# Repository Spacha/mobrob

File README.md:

# mobrob

A mobile robot 

## Features

* Obstacle detection and avoidance
* Room mapping (explore mode?)
* Manual control (throttle + steer)
  * For example, through browser-based GUI
* Automatic navigation (A to B) (after exploring space?)
  * Complete more complex tasks like _fetch an item_?
* Charging capability preferable (e.g. MCP73831)
  * https://www.youtube.com/watch?v=GRd9uTwg7r4&ab_channel=MicroTypeEngineering
  * https://www.youtube.com/watch?v=TyaW8ZKumno&ab_channel=PlumPot

# Initial design

Datasheets for components are found in `Datasheets` folder.

* **Processor & connectivity**: ESP8266 | [datasheet](datasheets/ESP8266EX_datasheet-v4.4.pdf)
  * These values are for ESP8266EX
  * WiFi: 802.11 b/g/n Wifi, 2.4-2.5 GHz
  * Peripherals: UART / SDIO / SPI / I2C / I2S / IR Remote Control / GPIO / PWM
  * Operating voltage 3.3V (3.0-3.6V)
  * Average operating current: 80 mA
  * Around 50 kB RAM (for user, when connected to a station)
  * **Requires external SPI flash!** Up to 16 MB flash can be supported
    * Suggested: 512 kB (without OTA), 1 MB (with OTA)
  * Single core, 80 MHz
* **Dual H-bridge motor driver**: L293D | [datasheet](datasheets/L293x_datasheet.pdf)
* Power management:
  * **Battery**: 11.1V Li-Po (6-12V), (3 x 3.7V cells)
    * Price: $20-40
  * **Buck converter (12V->5V)**: LM2596 or other...
    * https://www.youtube.com/watch?v=C7-8nUU6e3E&t=2367s
  * **LDO (5V->3.3V)**: LM7805
    * https://electronics.stackexchange.com/questions/420999/use-5v-linear-regulator-and-ldo-3-3v

* **Motors & chassis**: Dual motor tank chassis (3-7V)
  * https://www.aliexpress.com/item/4000115994387.html?spm=a2g0o.order_list.0.0.21ef1802jPbMxm
  * Has slot for 4xAA batteries, could be modified to fit the rechargable 3-cell Li-Po battery.
  * Size: 9.7cm x 18.5cm x 5cm (width x length x height )
  * Motors: 130 size generic, can be replaced if necessary
  * Price: $18.50

* Sensors (both for proximity and distance, and other):
  * IMU?
  * UT/IR?
  * Others?

# Discussion

I am not sure if either ESP32 or ESP8266 come in QFP format (only in QFN, no-leads). I guess JLCPCB and others also assemble these devices so maybe this is not an issue.

## ESP32
ESP32 would be considerably better than ESP8266. It has a lot more functionality and also has 8MB of onboard flash (ESP32-S3FN8, see ESP32-S3 datasheet, p.11).

* https://www.youtube.com/watch?v=WWIy6a0T7WM&ab_channel=PlumPot
* Decoupling caps (as close of the pins as possible)
* External crystal? (see Phil's lab)
* Note the antenna/RF part!
  * No traces (or any copper) beneath the antenna part!
* Careful with differential pairs

* https://en.wikipedia.org/wiki/ESP32#ESP32-S3:
  * ESP32-WROOM-32D: PCB trace antenna, 4 MiB flash (probably preferable)
  * ESP32-WROOM-32U: U.FL socket antenna, 4 MiB flash

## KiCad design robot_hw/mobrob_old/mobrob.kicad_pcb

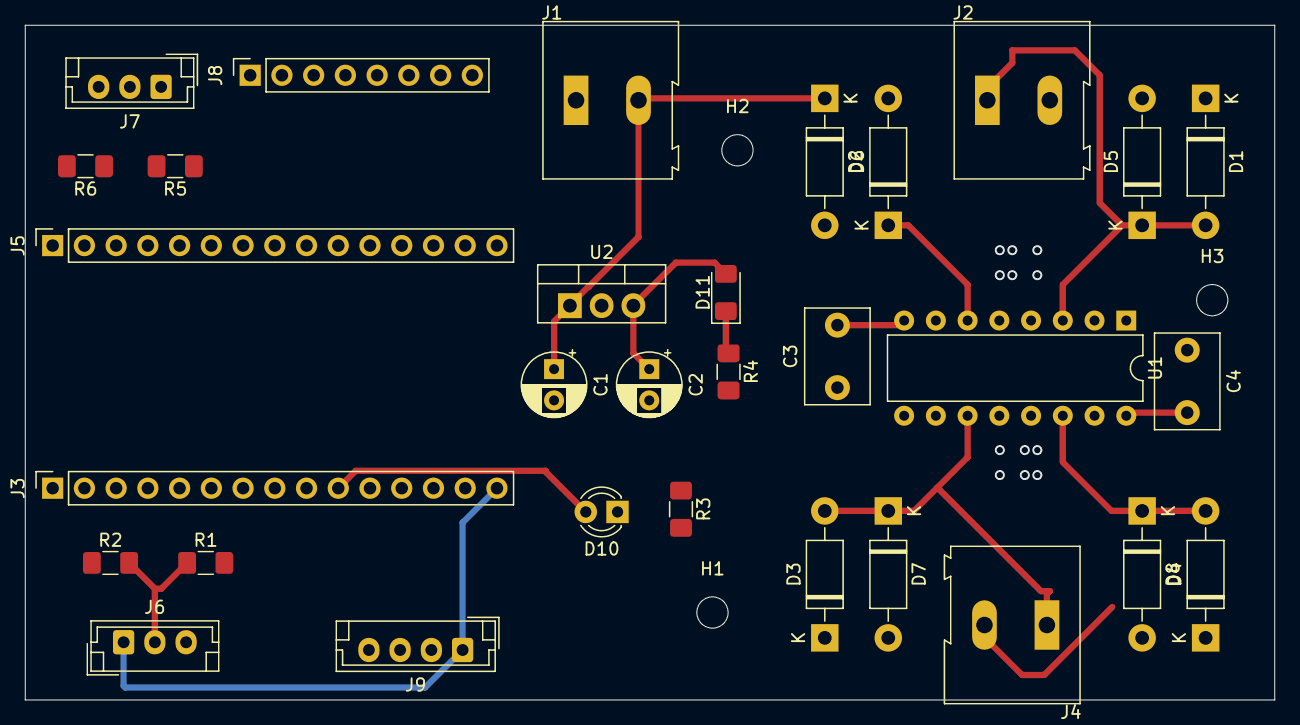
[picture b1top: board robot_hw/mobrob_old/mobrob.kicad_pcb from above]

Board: 2 copper layers, 100.0 x 54.0 mm, 34 parts (0 on the bottom side), 24 nets.

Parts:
C1: 0.22uF; CP_Radial_D5.0mm_P2.50mm
C2: 0.1uF; CP_Radial_D5.0mm_P2.50mm
C3, C4: 0.1uF; C_Disc_D7.5mm_W5.0mm_P5.00mm
D1, D2, D3, D4, D5, D6, D7, D8: 1N4007; D_DO-41_SOD81_P10.16mm_Horizontal
D10: LED_STATUS; LED_D3.0mm
D11: LED_POWER; LED_1206_3216Metric_Pad1.42x1.75mm_HandSolder
H1, H2, H3: MountingHole; MountingHole_2.5mm
J1: POWER; TerminalBlock_Altech_AK300-2_P5.00mm
J2: RMOTOR_OUT; TerminalBlock_Altech_AK300-2_P5.00mm
J3: MCU_ROW1; PinSocket_1x15_P2.54mm_Vertical
J4: LMOTOR_OUT; TerminalBlock_Altech_AK300-2_P5.00mm
J5: MCU_ROW2; PinSocket_1x15_P2.54mm_Vertical
J6: LHALL; JST_EH_B3B-EH-A_1x03_P2.50mm_Vertical
J7: RHALL; JST_EH_B3B-EH-A_1x03_P2.50mm_Vertical
J8: IMU; PinSocket_1x08_P2.54mm_Vertical
J9: UT; JST_EH_B4B-EH-A_1x04_P2.50mm_Vertical
R1, R6: 33k; R_1206_3216Metric_Pad1.42x1.75mm_HandSolder
R2, R5: 15k; R_1206_3216Metric_Pad1.42x1.75mm_HandSolder
R3, R4: 150; R_1206_3216Metric_Pad1.42x1.75mm_HandSolder
U1: L293D; DIP-16_W7.62mm
U2: L7805; TO-220-3_Vertical

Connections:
1,2EN: J3.7, U1.1
1A: J3.6, U1.2
2A: J3.12, U1.7
3,4EN: J3.9, U1.9
3A: J3.8, U1.10
4A: J3.13, U1.15
+5V: C2.1, C4.2, D11.2, J3.15, J6.1, J7.1, J8.1, J9.1, U1.16, U2.3
+12V: C1.1, C3.2, D1.1, D2.1, D3.1, D4.1, J1.2, U1.8, U2.1
GND: C1.2, C2.2, C3.1, C4.1, D5.2, D6.2, D7.2, D8.2, J1.1, J3.14, J5.14, J6.3, J7.3, J8.2, J9.4, R1.2, R3.1, R4.2, R6.2, U1.4, U1.5, U1.12, U1.13, U2.2
IMU_SCL: J5.2, J8.3
IMU_SDA: J5.5, J8.4
LED_STATUS: D10.2, J3.10
LHALL_IN: J3.3, R2.1
unnamed: D1.2, D5.1, J2.1, U1.3
unnamed: D2.2, D6.1, J2.2, U1.6
unnamed: D3.2, D7.1, J4.1, U1.11
unnamed: D4.2, D8.1, J4.2, U1.14
unnamed: D10.1, R3.2
unnamed: D11.1, R4.1
unnamed: J6.2, R1.1, R2.2
unnamed: J7.2, R5.2, R6.1
RHALL_IN: J3.2, R5.1
UT_ECHO: J5.1, J9.3
UT_TRIG: J5.11, J9.2

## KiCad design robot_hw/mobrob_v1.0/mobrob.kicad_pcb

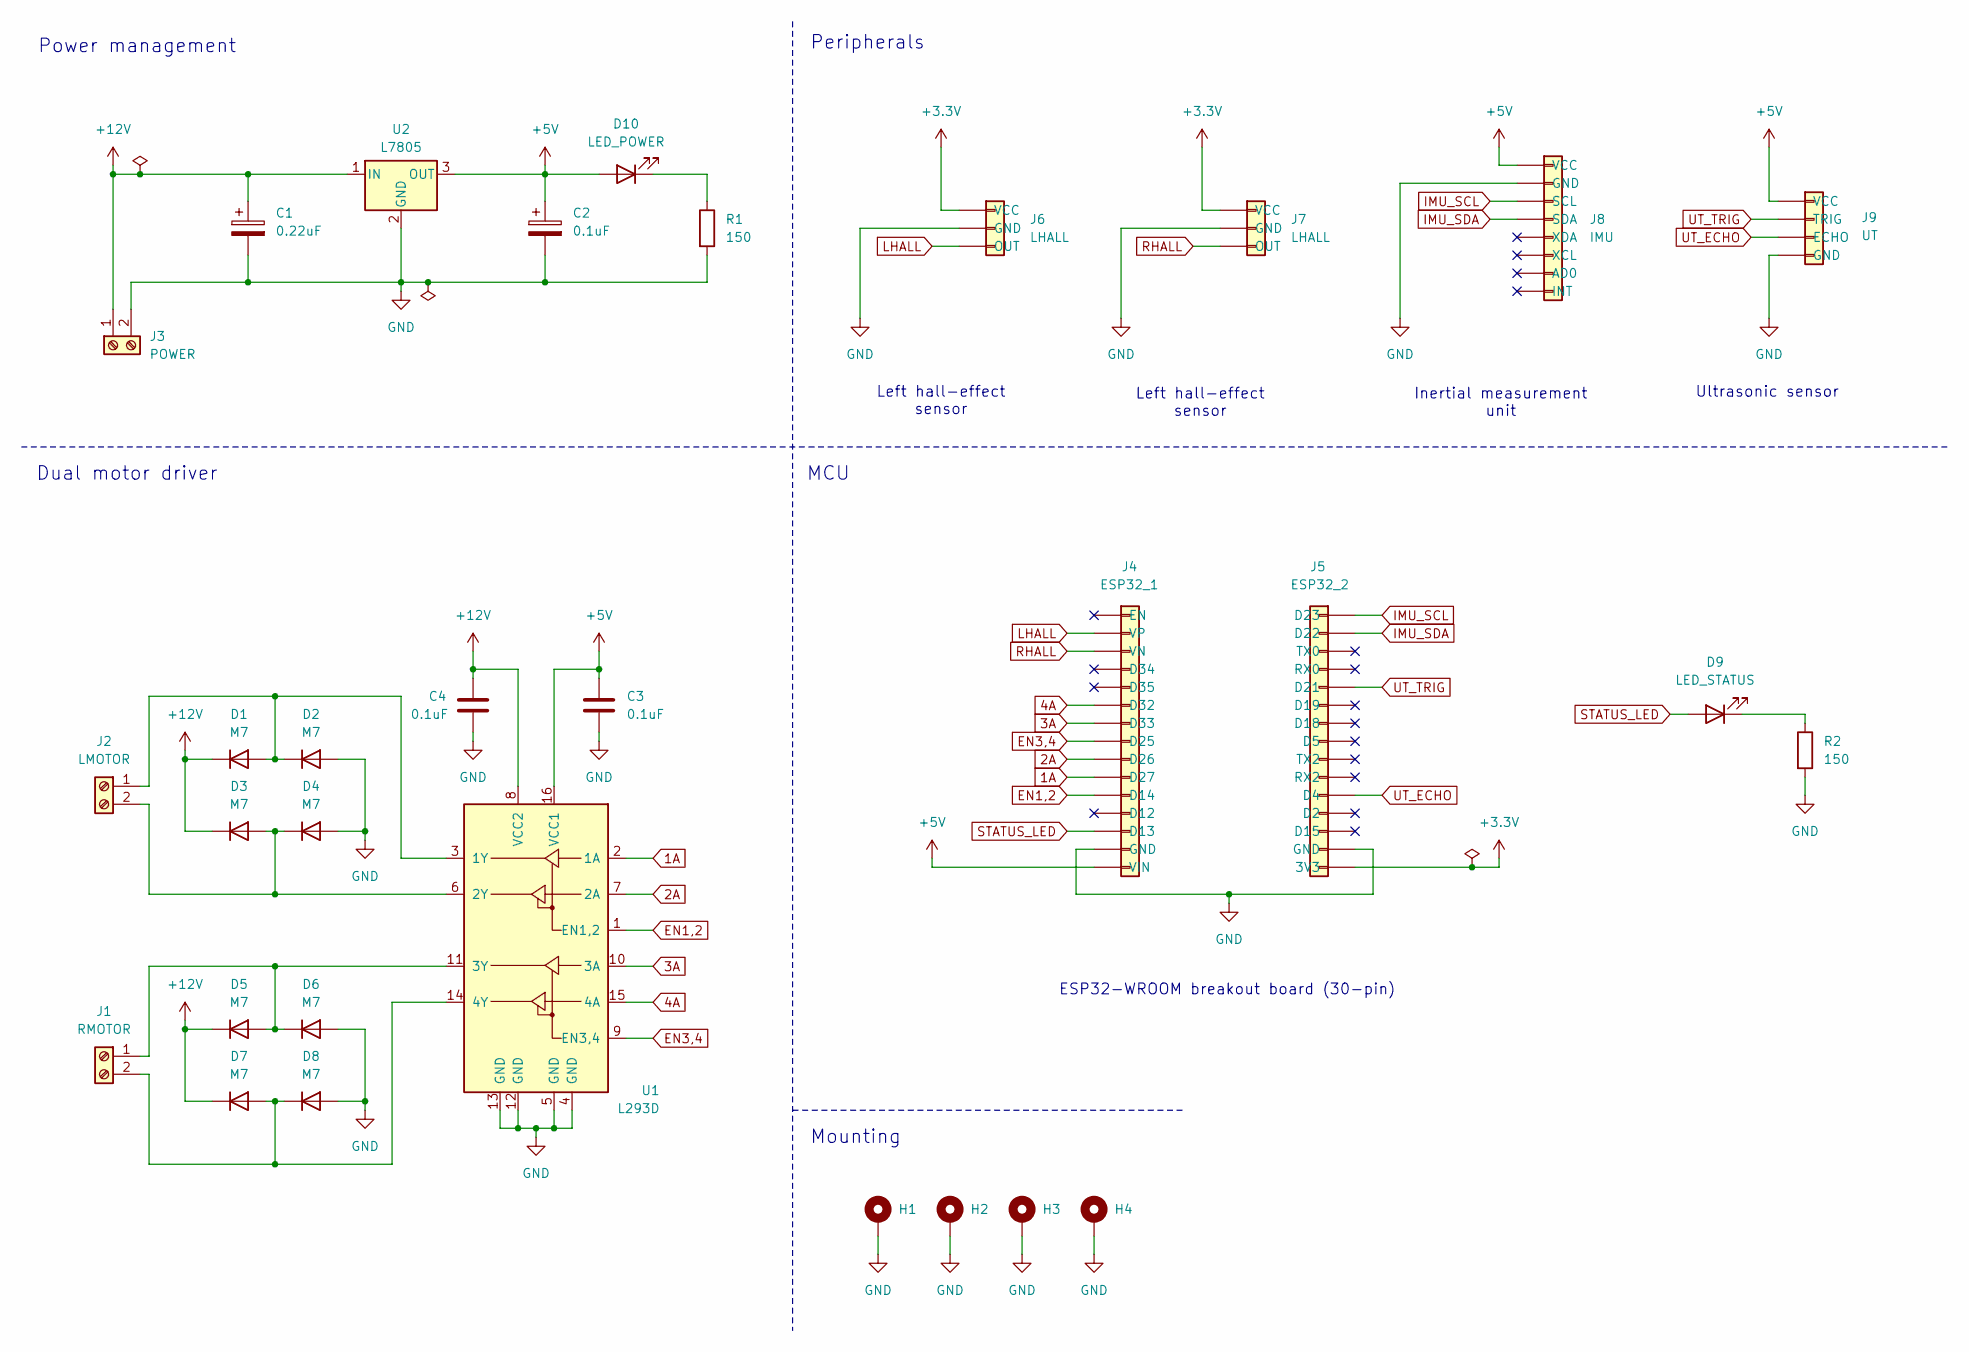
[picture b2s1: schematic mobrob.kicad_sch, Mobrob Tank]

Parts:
C1: 0.22uF; CP_Radial_D10.0mm_P5.00mm
C2: 0.1uF; CP_Radial_D10.0mm_P5.00mm
C3, C4: 0.1uF; C_1206_3216Metric_Pad1.33x1.80mm_HandSolder
D1, D2, D3, D4, D5, D6, D7, D8: M7; D_SMA_Handsoldering
D9: LED_STATUS; LED_D5.0mm
D10: LED_POWER; LED_1206_3216Metric_Pad1.42x1.75mm_HandSolder
H1, H2, H3, H4: MountingHole_Pad; MountingHole_3.2mm_M3_Pad_Via
J1: RMOTOR; TerminalBlock_Phoenix_PT-1,5-2-3.5-H_1x02_P3.50mm_Horizontal
J2: LMOTOR; TerminalBlock_Phoenix_PT-1,5-2-3.5-H_1x02_P3.50mm_Horizontal
J3: POWER; TerminalBlock_Phoenix_PT-1,5-2-3.5-H_1x02_P3.50mm_Horizontal
J4: ESP32_1; PinSocket_1x15_P2.54mm_Vertical
J5: ESP32_2; PinSocket_1x15_P2.54mm_Vertical
J6, J7: LHALL; PinHeader_1x03_P2.54mm_Vertical
J8: IMU; PinSocket_1x08_P2.54mm_Vertical
J9: UT; PinHeader_1x04_P2.54mm_Vertical
R1, R2: 150; R_0805_2012Metric_Pad1.20x1.40mm_HandSolder
U1: L293D; DIP-16_W7.62mm
U2: L7805; TO-220-3_Vertical

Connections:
1A: J4.10 (D27), U1.2 (1A)
2A: J4.9 (D26), U1.7 (2A)
3A: J4.7 (D33), U1.10 (3A)
4A: J4.6 (D32), U1.15 (4A)
+3.3V: J5.15 (3V3), J6.1 (VCC), J7.1 (VCC)
+5V: C2.1, C3.1, D10.2 (A), J4.15 (VIN), J8.1 (VCC), J9.1 (VCC), U1.16 (VCC1), U2.3 (OUT)
+12V: C1.1, C4.1, D1.1 (K), D3.1 (K), D5.1 (K), D7.1 (K), J3.1, U1.8 (VCC2), U2.1 (IN)
EN1,2: J4.11 (D14), U1.1 (EN1,2)
EN3,4: J4.8 (D25), U1.9 (EN3,4)
GND: C1.2, C2.2, C3.2, C4.2, D2.2 (A), D4.2 (A), D6.2 (A), D8.2 (A), H1.1, H2.1, H3.1, H4.1, J3.2, J4.14 (GND), J5.14 (GND), J6.2 (GND), J7.2 (GND), J8.2 (GND), J9.4 (GND), R1.2, R2.2, U1.4 (GND), U1.5 (GND), U1.12 (GND), U1.13 (GND), U2.2 (GND)
IMU_SCL: J5.1 (D23), J8.3 (SCL)
IMU_SDA: J5.2 (D22), J8.4 (SDA)
LHALL: J4.2 (VP), J6.3 (OUT)
unnamed: D1.2 (A), D2.1 (K), J2.1, U1.3 (1Y)
unnamed: D3.2 (A), D4.1 (K), J2.2, U1.6 (2Y)
unnamed: D5.2 (A), D6.1 (K), J1.1, U1.11 (3Y)
unnamed: D7.2 (A), D8.1 (K), J1.2, U1.14 (4Y)
unnamed: D9.1 (K), R2.1
unnamed: D10.1 (K), R1.1
RHALL: J4.3 (VN), J7.3 (OUT)
STATUS_LED: D9.2 (A), J4.13 (D13)
UT_ECHO: J5.11 (D4), J9.3 (ECHO)
UT_TRIG: J5.5 (D21), J9.2 (TRIG)

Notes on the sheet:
Power management
Dual motor driver
MCU
Left hall-effect sensor
Mounting
ESP32-WROOM breakout board (30-pin)
Inertial measurement unit
Peripherals
Ultrasonic sensor

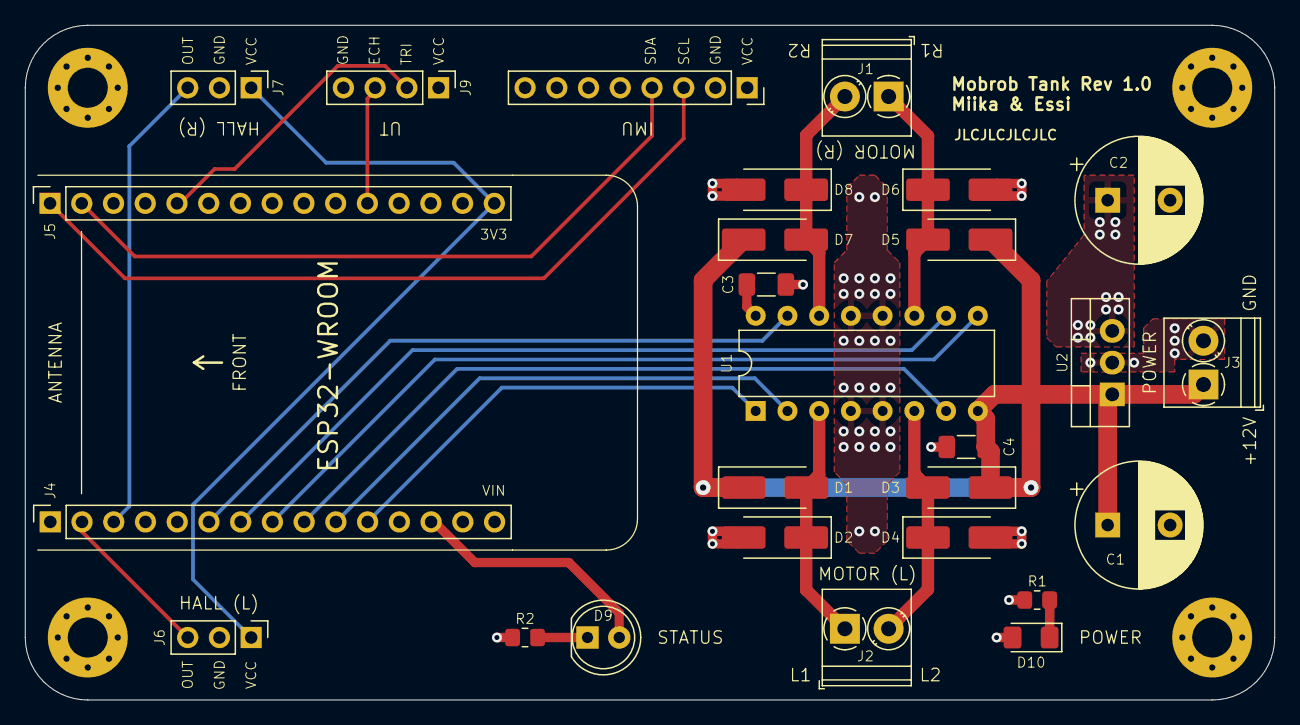
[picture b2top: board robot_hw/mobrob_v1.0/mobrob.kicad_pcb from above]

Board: 4 copper layers, 100.0 x 54.0 mm, 31 parts (0 on the bottom side), 23 nets.

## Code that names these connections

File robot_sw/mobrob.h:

#ifndef __MOBROB_H__
#define __MOBROB_H__

#include "network_credentials.h"

#define FW_VERSION "1.0.0"

// If defined, the debug mode is enabled, which allows:
// * Verbose logging to serial
// * Serial control interface
#define __DEBUG__

///////////////////////////////////////////////////////////////////////////////
// Pin assignments
///////////////////////////////////////////////////////////////////////////////

#define PIN_STATUS_LED  13

#define PIN_UT_TRIG     21
#define PIN_UT_ECHO      4
#define PIN_IMU_SDA     22
#define PIN_IMU_SCL     23
#define PIN_LHALL       36
#define PIN_RHALL       39

#define PIN_LEN         14    // Left motor enable:     3,4EN
#define PIN_L1          27    // Left motor control 1:  3A
#define PIN_L2          26    // Left motor control 2:  4A
#define PIN_REN         25    // Right motor enable:    1,2EN
#define PIN_R1          33    // Right motor control 1: 1A
#define PIN_R2          32    // Right motor control 2: 2A

///////////////////////////////////////////////////////////////////////////////

#ifndef __DEBUG__
#define PRINT(s) Serial.print(s);
#define PRINTLN(s) Serial.println(s);
#else
#define PRINT(s)
#define PRINTLN(s)
#endif

#if CONFIG_FREERTOS_UNICORE
# define ARDUINO_RUNNING_CORE 0
#else
# define ARDUINO_RUNNING_CORE 1
#endif

///////////////////////////////////////////////////////////////////////////////
// Definitions
///////////////////////////////////////////////////////////////////////////////

enum Status { UNCONNECTED, CONNECTED };
enum Mode { MANUAL = 0, EXPLORE = 1 };

///////////////////////////////////////////////////////////////////////////////
// Forward declarations
///////////////////////////////////////////////////////////////////////////////

void update_configuration(float track_speed, Mode mode);
void control(float left_track, float right_track);

void TaskControl(void *params);
void TaskKeepWifiAlive(void *params);
void TaskSendUpdate(void *params);
void TaskReceiveSerial(void *params);
void TaskBlink(void *params);

#endif /* __MOBROB_H__ */

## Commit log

2022-04-01 Initial structure and design
2022-04-01 Updated design, added ESP datasheet
2022-04-01 Design
2023-03-14 Working motor demo for ESP32
2023-03-14 Added UDP receiver which can now receive messages from ESP32
2023-03-14 UDP packets now flow to both directions
2023-03-14 Moved network credentials to a hidden file for security
2023-03-14 Trying to get remote control working
2023-04-17 New datasheets
2023-04-17 Test code for L293DNE and other testing
2023-04-19 Added and tried various UDP examples. Improved server.
2023-04-19 Started a UI app for the server
2023-04-19 Capture keyboard and send live commands
2023-04-19 Server: key whitelist, show more messages
2023-04-19 Finally control motors from the server
2023-04-22 Movement control for the robot
2023-04-22 Robot speed control from server
2023-04-22 Added some datasheets
2023-04-24 Added ultrasonic sensor, some refactoring
2023-06-01 UT measurement, control flows and more
2023-06-01 Added a timed task for async tasking
2023-06-13 Implemented the robot SW using FreeRTOS
2023-06-13 Separated network credentials to an untracked header
2023-08-06 New log viewer widget
2023-08-17 Minor cleanup in the robot code
2023-08-17 Added __pycache__ to gitignore
2023-08-17 Double click to open log message in a dialog
2023-08-17 Added the map view with a simple robot sprite
2023-09-13 Dashboard: Clear log
2023-09-13 WIP: Cycle detection
2023-09-13 Python scripts for cycle analysis
2023-09-24 Track robot angle - very WIP
2024-04-13 Started major cleanup and refactoring
2024-04-13 Started working on new server
2024-04-15 Separated server and robust communication protocol
2024-04-15 Sketching the schematic
2024-06-16 Massive dump
2024-06-19 RSW: Drive completed
2024-06-21 New dashboard almost done
2024-06-21 Added sample credentials file
2024-06-25 Communication integration finally done
2024-06-25 Started working on robot controls
2024-06-25 Control widget done
2024-06-26 Robot control works at last
2024-06-26 Started work on sensors - UT done
2024-06-26 IMU sensor done
2024-06-26 Attitude widget done
2024-06-26 Dashboard title updated
2024-06-26 Removed old HW project
2024-06-26 Started test development for robot - Motor and Drive done
2024-06-27 Server done
2024-06-27 Removed backyard
2024-06-27 All tests done. Obstacle widget done. Project done.
2024-06-27 Documentation comments done
2024-06-27 Added missing comments to Drive
